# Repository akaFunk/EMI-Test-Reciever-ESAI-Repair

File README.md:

# Adapters for capacitor replacemnt in an Rohde & Schwarz EMI Test Receiver ESAI
We got an old Rohde & Schwarz EMI Test Receiver ESAI which needed a little repair. The device did not boot when turning it on. Just a few LEDs switched on and nothing more happend. It turned out that two capacitors were shorting one of the power rails. Additionally the responsible fuse was blown. We decided to replace all capacitors to be on the safe side. The file ReplacementCaps.ods gives an overview of the capacitors in the two devices and the possible replacement parts. For the values 4700, 10000 and 2200 µF we were able to find fitting replacements. For the capacitors with the values 15000 and 470 µF we had to use replacements with different footprints. Two PCBs were designed to adapt the two different footprints to the original ones.

## Images

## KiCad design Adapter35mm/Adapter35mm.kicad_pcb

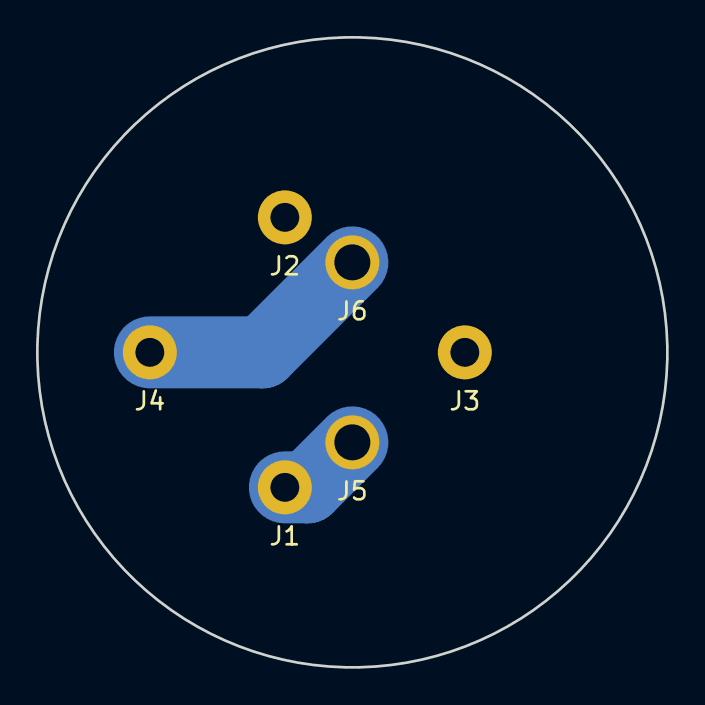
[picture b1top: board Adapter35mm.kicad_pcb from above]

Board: 2 copper layers, 35.0 x 35.0 mm, 6 parts (0 on the bottom side), 2 nets.

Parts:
J1: Orig1; Hole_1.3mm
J2: Orig2; Hole_1.3mm
J3: Orig3; Hole_1.3mm
J4: Orig-; Hole_1.3mm
J5: Cap+; Hole_1.7mm
J6: Cap-; Hole_1.7mm

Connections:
unnamed: J1.1, J5.1
unnamed: J4.1, J6.1

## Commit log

2018-08-16 Initial version
